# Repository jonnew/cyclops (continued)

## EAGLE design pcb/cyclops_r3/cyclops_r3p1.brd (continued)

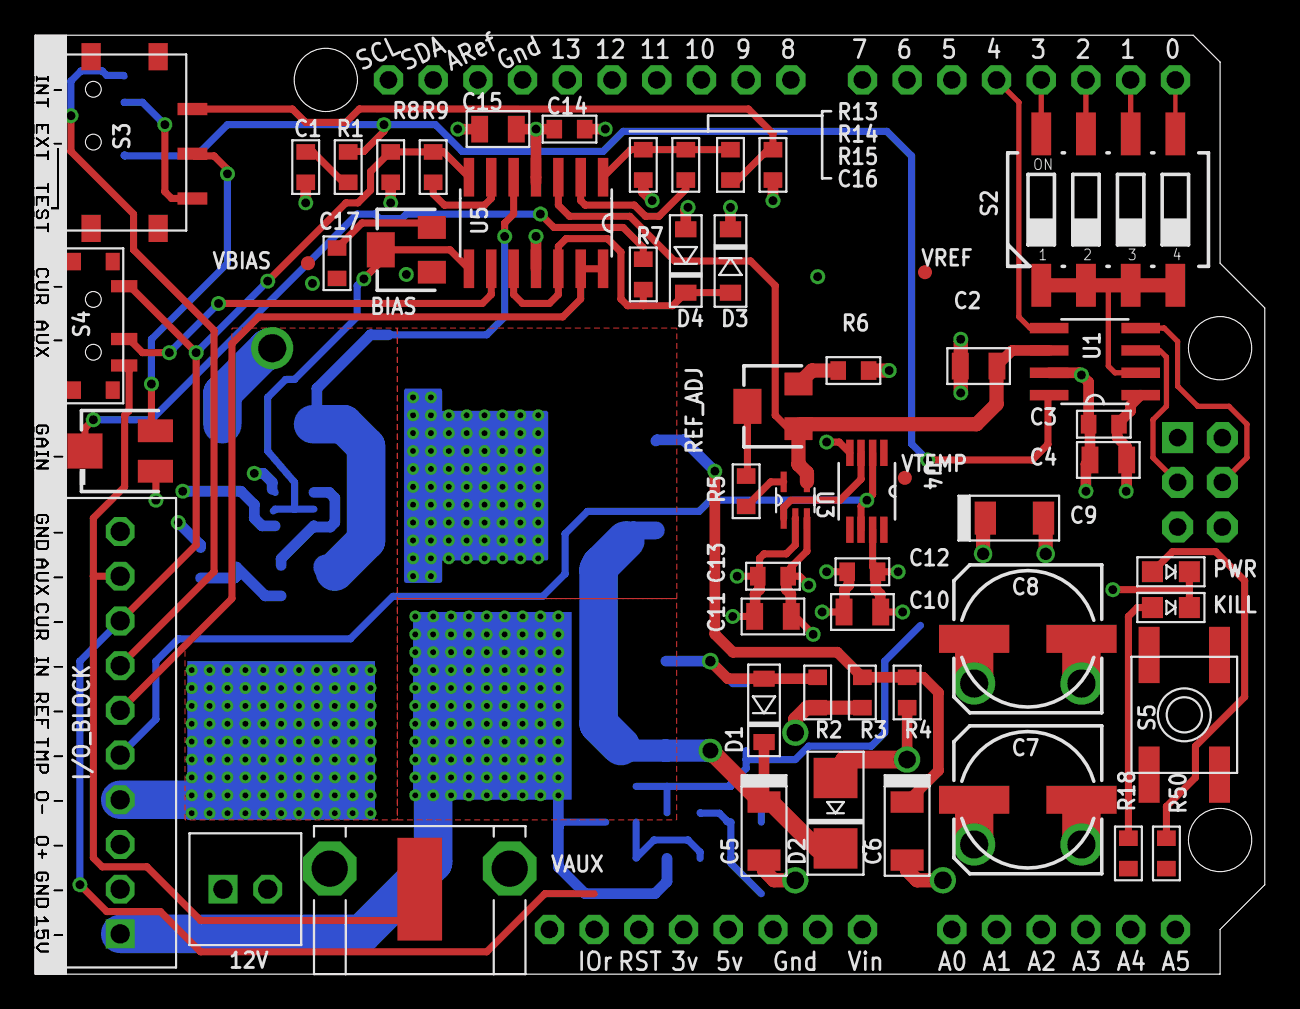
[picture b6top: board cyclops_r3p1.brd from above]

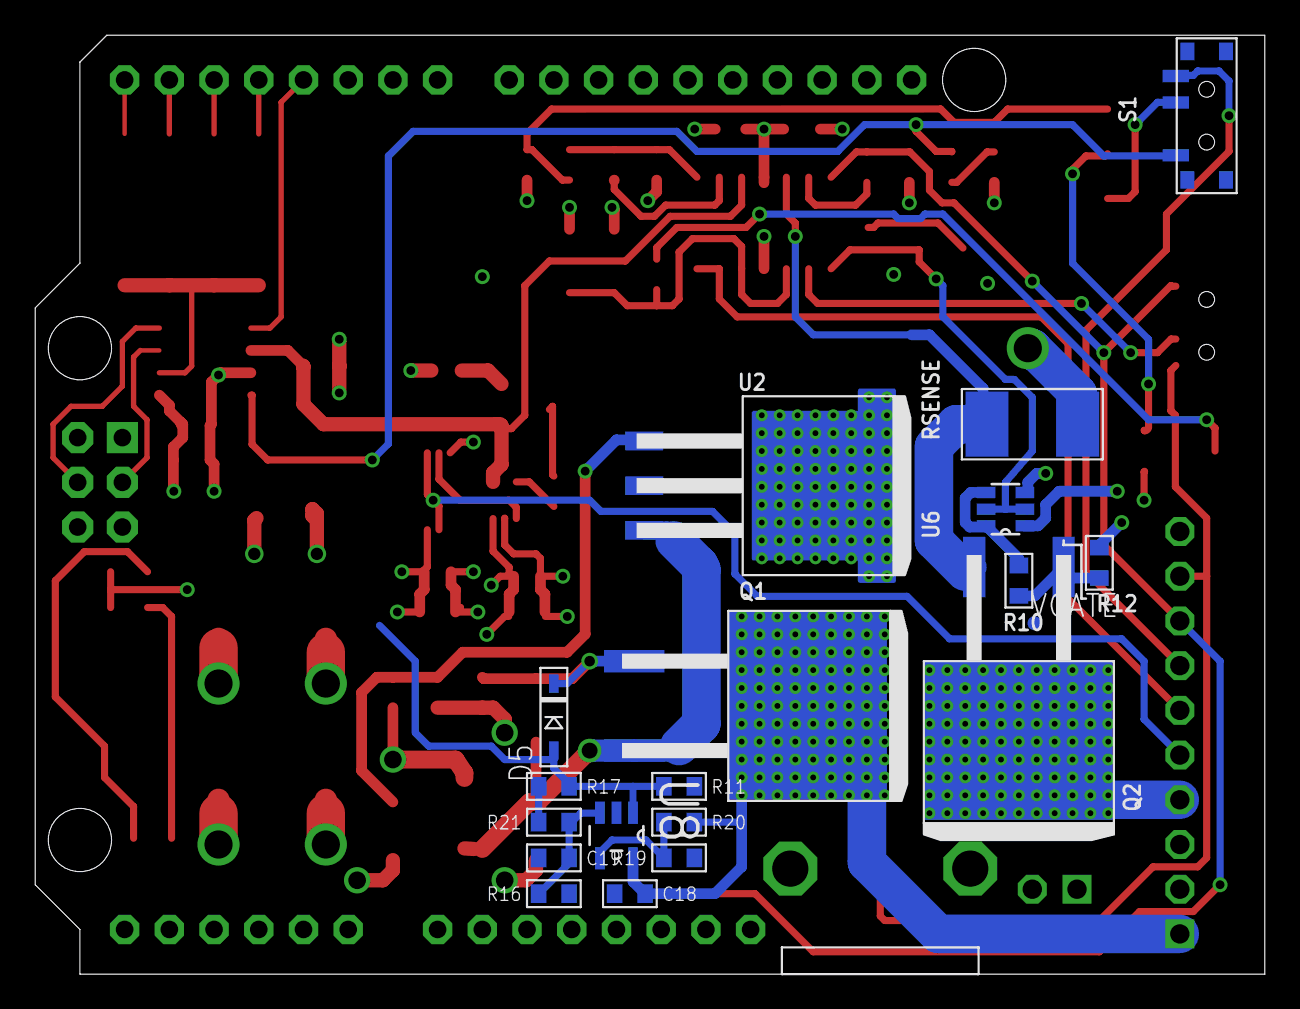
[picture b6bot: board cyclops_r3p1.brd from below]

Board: 4 copper layers, 69.8 x 53.3 mm, 74 parts (19 on the bottom side), 47 nets.

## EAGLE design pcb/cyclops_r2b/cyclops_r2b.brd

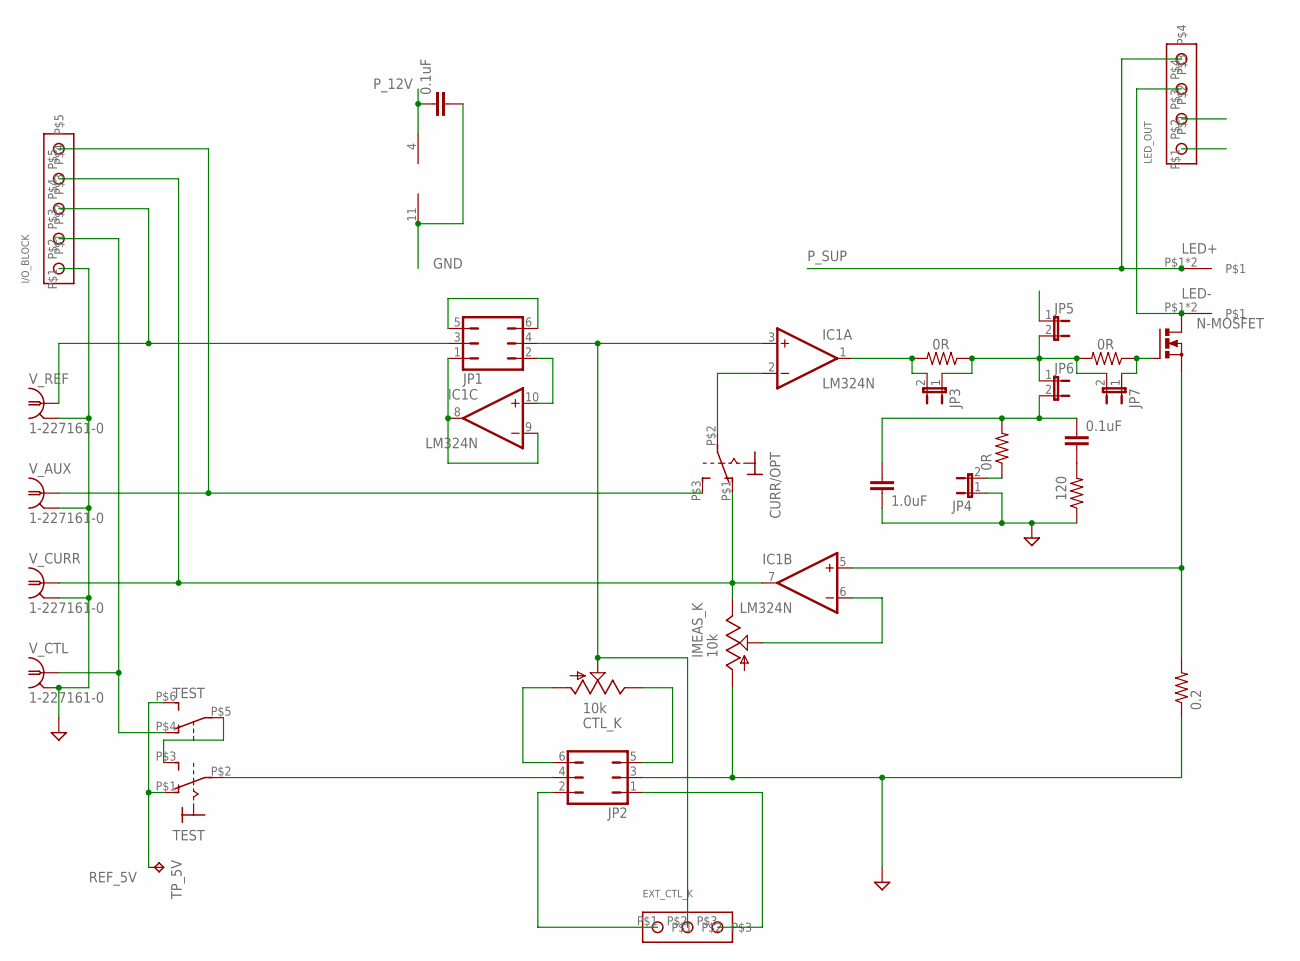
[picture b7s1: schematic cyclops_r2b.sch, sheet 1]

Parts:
C1, C3: 0.1uF; C050-024X044
C2: 1.0uF; C025-024X044
CTL_K: 10k; RJ6S
CURR/OPT: SPST_SWITCH; A_TOGGLE_SPST
EXT_CTL_K: SCREW3
I/O_BLOCK: SCREW5
IC1: LM324N; DIL14
IMEAS_K: 10k; RJ6S
JP1, JP2: JP3Q
JP3, JP4, JP5, JP6, JP7: JP1E; JP1
LED+: BANANA_TO_BOARD
LED-: BANANA_TO_BOARD
LED_OUT: SCREW4
N-MOSFET: PMOSFET_NTO220BH; TO220BH
R1, R2, R4: 0R; 0207/7
R3: 120; 0207/7
R_CURR: 0.2; IMEAS_R
TEST: SP3T_SWITCH; 320-938
TP_5V: TPPAD1-13; P1-13
V_AUX: 1-227161-0; AMP_227161
V_CTL: 1-227161-0; AMP_227161
V_CURR: 1-227161-0; AMP_227161
V_REF: 1-227161-0; AMP_227161

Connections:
GND: C1.2, C2.2, I/O_BLOCK.P$1, IC1.11 (V-), IMEAS_K.A, JP2.3, JP4.1, LED_OUT.P$1, R3.1, R_CURR.1, V_AUX.2 (GND), V_CTL.2 (GND), V_CURR.2 (GND), V_REF.2 (GND); also elsewhere on the board
unnamed: CURR/OPT.P$2, IC1.2 (-IN)
unnamed: IC1.5 (+IN), N-MOSFET.S, R_CURR.2
unnamed: IC1.1 (OUT), JP3.2, R1.2
unnamed: CURR/OPT.P$1 (O), I/O_BLOCK.P$4, IC1.7 (OUT), IMEAS_K.E, V_CURR.1
unnamed: CURR/OPT.P$3 (S), I/O_BLOCK.P$5, V_AUX.1
unnamed: JP2.4, TEST.P$2
unnamed: CTL_K.E, JP2.5
unnamed: CTL_K.S, EXT_CTL_K.P$2, IC1.3 (+IN), JP1.4
unnamed: IC1.8 (OUT), IC1.9 (-IN), JP1.1
unnamed: I/O_BLOCK.P$2, TEST.P$4 (O), V_CTL.1
unnamed: C2.1, C3.1, JP6.2, R2.2
unnamed: CTL_K.A, JP2.6
unnamed: C3.2, R3.2
unnamed: IC1.10 (+IN), JP1.2
unnamed: IC1.6 (-IN), IMEAS_K.S
unnamed: JP1.5, JP1.6
unnamed: I/O_BLOCK.P$3, JP1.3, V_REF.1
unnamed: LED-.P$1, LED-.P$2, LED_OUT.P$3, N-MOSFET.D
unnamed: TEST.P$3 (S), TEST.P$5
unnamed: EXT_CTL_K.P$1, JP2.2
unnamed: EXT_CTL_K.P$3, JP2.1
unnamed: JP4.2, R2.1
unnamed: JP3.1, JP5.2, JP6.1, JP7.2, R1.1, R4.2
unnamed: JP7.1, N-MOSFET.G, R4.1
P_12V: C1.1, IC1.4 (V+), LED_OUT.P$2; also elsewhere on the board
P_SUP: LED+.P$1, LED+.P$2, LED_OUT.P$4; also elsewhere on the board
REF_5V: TEST.P$1 (O), TEST.P$6 (S), TP_5V.TP; also elsewhere on the board

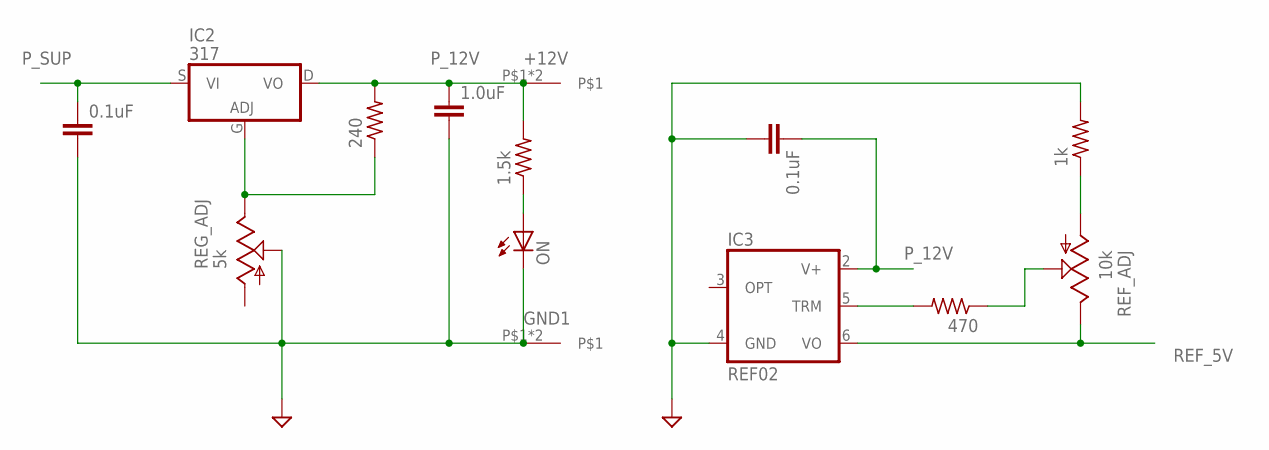
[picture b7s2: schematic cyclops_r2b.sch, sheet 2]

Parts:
+12V: BANANA_TO_BOARD
C4, C6: 0.1uF; C050-024X044
C5: 1.0uF; C025-024X044
GND1: BANANA_TO_BOARD
IC2: 317; TO220BH
IC3: REF02; DIL08-OVAL
ON: LED3MM
R5: 240; 0207/7
R6: 1.5k; 0207/7
R7: 470; 0207/7
R8: 1k; 0207/7
REF_ADJ: 10k; RJ6S
REG_ADJ: 5k; RJ6S

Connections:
GND: C4.2, C5.2, C6.2, GND1.P$1, GND1.P$2, IC3.4 (GND), ON.K (C), R8.2, REG_ADJ.S; also elsewhere on the board
unnamed: IC2.G (ADJ), R5.1, REG_ADJ.E
unnamed: IC3.5 (TRM), R7.2
unnamed: R7.1, REF_ADJ.S
unnamed: R8.1, REF_ADJ.A
unnamed: ON.A, R6.1
P_12V: +12V.P$1, +12V.P$2, C5.1, C6.1, IC2.D (VO), IC3.2 (V+), R5.2, R6.2; also elsewhere on the board
P_SUP: C4.1, IC2.S (VI); also elsewhere on the board
REF_5V: IC3.6 (VO), REF_ADJ.E; also elsewhere on the board

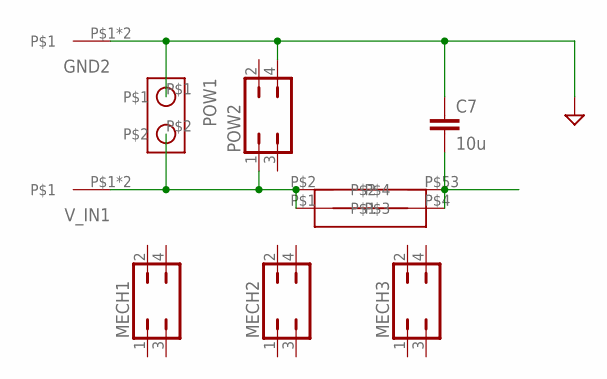
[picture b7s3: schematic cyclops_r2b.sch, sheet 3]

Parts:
C7: 10u; C025-024X044
GND2: BANANA_TO_BOARD
MECH1, MECH2, MECH3: JP2Q
POW1: SCREW2
POW2: JP2Q
U$1: FUSE >2A; NXT-FUSE
V_IN1: BANANA_TO_BOARD

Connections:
GND: C7.1, GND2.P$1, GND2.P$2, POW1.P$1, POW2.4; also elsewhere on the board
P_SUP: C7.2, U$1.P$4, U$1.P$53; also elsewhere on the board
P_SUP_BEFORE: POW1.P$2, POW2.1, U$1.P$1, U$1.P$2, V_IN1.P$1, V_IN1.P$2

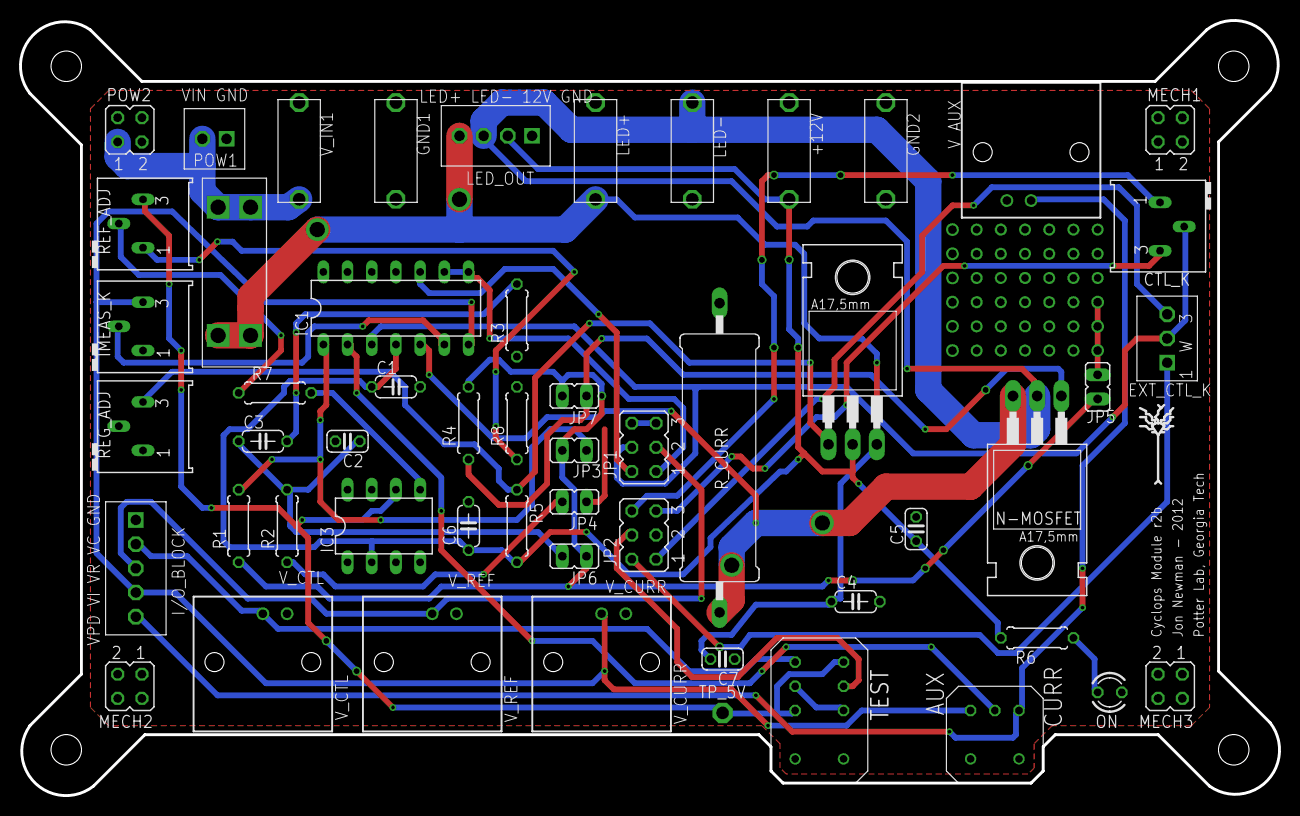
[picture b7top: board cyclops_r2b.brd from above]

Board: 2 copper layers, 132.2 x 81.4 mm, 54 parts (0 on the bottom side), 34 nets.

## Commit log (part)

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2014-08-21 Added digital overcurrent protection.
2014-08-22 Minor cleanup.
2014-08-24 Removed temp vim files.
2014-09-04 Cleaned up BOM.
2014-09-04 Slight BOM update.
2014-09-15 Final very minor changes to r3.3. before fabrication.
2014-10-04 More work on driver.
2014-10-06 The base library is functional. Includes over-current protection and waveform generation features.
2014-10-06 Work on trigger interupt handling.
2014-10-07 Added an over-current protection example.
2014-10-10 Front panel dimensions have been tested and look good. Started integrating light pipes on front panel LEDs. The LEDs need to be moved and swapped for normal verical ones.
2014-10-14 Finished front and rear panel layout. Started PCB version.
2014-10-15 Organization.
2014-10-21 Minor updates.
2014-10-26 Some layout changes to make ergonomic. Updated BOM.
2014-10-30 Almost done with panels.
2014-10-30 BOM update.
2014-11-09 Added automatic logic level conversion on trigger line.
2014-11-16 Updated TODO.
2014-11-20 Added a note.
2014-11-22 More spice simulations.
2014-11-23 Spice update.
2014-11-24 Added spice simulation of negative rail generation.
2014-11-25 New schematic should be finished. Double check and then layout board.
2014-11-26 Started laying out switching inverter.
2014-11-30 More layout.
2014-12-19 Updates to TODO. Fixed MAX4564 package type.
2014-12-21 Layout of rev. 3.5. It needs to be double checked before fabrication.
2014-12-21 Minor layout changes.
2014-12-22 Updated panels for revision 3.5. Updated BOM for revision 3.5. Did inventory check to see what nees to be ordered.
2014-12-23 Almost ready to fabricate PCB. I need to do one last look over, concentrating on schematic.
2014-12-26 Built the LT1963 circuit next to the LM317, I will now replace the LM317.
2014-12-26 Added LM1936 to the board.
2014-12-28 Updated BOM and small layout changes. Ready to print.
2014-12-30 Ready to fabricate. This is revision 3.5.
2015-01-03 Minor BOM update.
2015-01-19 More TODOs and small fixes to circuit.
2015-01-22 Implemented some more TODOs.
2015-01-31 Small changes to spice. Need to bench test.
2015-02-08 Made schematic changes after testing latest spice simulations at the bench.
2015-02-15 Updated gerbers to rev 3.5A.
2015-02-16 Changed the test point labels, again.
2015-02-17 Started implementing documentation.
2015-02-25 Fixed the front panel design. This is revision 3.5A.
2015-02-25 Documentation updates.
2015-02-28 Updated PDF version of schematic.
2015-03-29 Refixed the incorrect labels on the jumper pads.
2015-04-02 More TODOs
2015-04-12 Started updating the docs
    - These will eventually be moved into the README.md
    - Need to integrate figures and create a mirrored PDF using pandoc.
2015-05-31 Minor README.md update.
2015-06-08 Got rid of negative supply source jumper.
2015-06-13 Rename file.
2015-07-02 DOC.md update.
2015-07-21 Sung-Yon is uploading some Cyclops pictures while trying to learn GitHub
2015-07-28 Fixed image display issue in DOC.md.
2015-07-28 jon's and my edit caused conflicts
2015-07-28 trying capitalized .JPG for Figs 3 and 4
2015-07-29 Updates to DOC.md. Need to think about how to make markdown pandoc friendly.
2015-07-30 More organization.
2015-07-30 Resize images to 400px max.
2015-07-30 Updates to DOC.md to make more pandoc friendly
    - I want to revert all the figure resizing changes because they look
    really bad now.
2015-08-02 Fixed file names.
2015-08-03 Updates to MANUAL.*.
2015-08-03 Many undates to MANUAL.md
    - About time to merge back into master branch.
    - All images reverted to original size
    - Manual is still under construction, but is complete enough to start
    being useful for people.
2015-08-04 Added some performance measures to the manual.
2015-08-05 Some minor updates to MANUAL.*
2015-08-19 Some recorganization and updates to manual.
2015-08-30 Minor silkscreen changes.
2015-10-30 A few changes made to comply with CircuitHub stuff
    - Almost ready to do a circuit hub run.
2015-12-02 Minor fix to the input circuit.
2015-12-15 Replaced edge mount BNC with cheaper alternative
    - Less than half the price
    - Much more available (made by molex)
    - Huge BOM money saver
    - Worried about production run with this many changes...
2015-12-17 Repo reorganization.
2015-12-31 Some very minor changes during final 3.5c assembly.
2016-01-04 Final changes to board after rev 3.5c construction and testing.
2016-01-27 File format update
    File is incorporated into the repo, rather than a text file with a url
    pointing at it. Removed date and spaces in title.
2016-01-28 Update MANUAL.md
    Markdown style retrieve link to Bilateral fiber coupled LED.
2016-02-03 Updates to QC procedure.
2016-02-03 README update.
2016-02-21 Lots of cleanup for 3.5D tag.
    - Got rid of versioning info in file names
    - Got rid of old BOM managment method since we can just point to
    circuithub instead
2016-02-21 More cleanup.
2016-02-21 Fixed broken links in manual.
2016-02-28 Nearly done with getting started guide.
    - There are couple of TODOs in the document that need to be taken care
    of
    - Document also points to full manual for documentaiton on some stuff
    (e.g. M8 connector install) that is not currently there.
2016-03-03 Documentation improvements.
2016-03-24 Small edit to kit manual.
2016-03-25 Forgot to add file.
2016-04-04 Update MANUAL.*
    - Fixes #3
    - Partially merged the kit assembly instructions with the main manual
    - Added a bunch of TODOs that generally concern interfacing the cyclops
    with external devices and LEDs, installing the Arudino, programming
    the Arrduino etc.
2016-04-04 More MANUAL.* updates
2016-04-19 Update README.md
    Added TODO for Rev. 3.6
2016-04-19 Tested Task objects (passed)
    Compiles and executes as expected.
    All Header field extraction using macros in RPC_defs.h, any change in RPC would reflect here, no need to change code elsewhere!
2016-04-19 Defined Waveform methodswq
2016-04-20 Added reset in Source, and Waveform example
    reset() is also virtual (since resetting sources cannot always be setting cur_ind = 0)
    Waveform example ping pongs between 2 (sin(t))^2 gen_Source objs
2016-05-03 Updated thorlabs LED connection instructions.
2016-05-07 Refactored the Waveform and Source classes
    Variables and class-names are better now.
    storedSource members are const*, so they won't edit the data arrays.
    Updated documentation.
    Apart from that made stylistic changes.
    Added keywords.txt
    Tested examples, made them more readable, less cluttered
2016-05-29 Modified Waveform to support scheduling. Added non-blocking SPI
    * nbSPI defines a few helper functions and an ISR for interrupt driven SPI
    * `Waveform::prepare`
    - begins an SPI transfer if in `PREPARING` state
    - can handle multi-byte transfers for a transaction.
    * `Cyclops::selectChip` and `Cyclops::deselectChip()` needed as all lookup tables are private.
    * Added the test for Queue.
2016-05-31 Added the Timer ISR, scheduler logic.
    * Using TimerOne library by Paul Stoffregen.
    * Waveform::process() is called by CPU scheduler
    * the `cyclops_timer_ISR` is pretty lightweight.
    * The pre-instantiated `waveformList` is the heart of this library.
2016-06-03 Source code reorganization.
2016-06-07 Added documentation and examples
    * nbSPI is not effective for Arduino devices, see docs/nbSPI
    * nbSPI tested [pass] and documented.
    * Added logo to docs :)
    * Fixed subtle bug in Waveform::outFrame_id, it should be initialised to DAC_BLOCK_SIZE.
2016-06-08 Fixed WaveformList (atleast for single channel)
    Now I can confidently start testing and porting on teensy
2016-06-11 Added head to head comparison table to MANUAL.md.
2016-06-15 Fixed Timer issues, made library.
    Also,
    * Waveform_t is complete. Can handle upto 4 channels
    * TimerOne fixed for our use.
    * Added example wave2_teensy. Uses latest libs
2016-06-17 More teensy layout.
2016-06-18 RPC draft implementation, see /src/teensy/rpc_loop
    * Serial comms are non-blocking
    * Fixed typos in RPC_defs.h (still buggy)
    * Added logic to task, Queue
    * Changed holdTime return type (once again) to uint32_t
    * Changed constructor calls to accomodate for N_SHOT, see wave2_teensy.ino
2016-06-21 RPC v1 implementation Complete \o/
    * added squareSource commands and changed LDAC temporarily
    * Fixed typo in ISR, also changed window size.
    * added RPC implementation in Task.cpp
    * added TScale, VScale, DC offset, squareSource, constHoldTime (for gen. Source)
    * 2 constructors for gen. Source
    * Tested rpc_loop.ino and all_waves.ino, other examples might be broken
2016-06-22 More docs and a CyclopsLib namespace
    * All stray functions or global vars are now in this namespace.
    * Added documentation on Task, readSerialAndPush, etc
    *
2016-07-05 Ticking off preparations for 3.6 layout.
2016-07-08 Lots of minor circuit mods
    - Replace OC SPDT with a SPST with better bandwidth and larger voltage
    rail capabilities since id does not need the other terminal
    - Spice modeling of input circuitry
    - Etc
2016-07-10 Started addining buck converter for digital rail.
2016-07-12 Almost done with layout.
2016-07-14 More routing. Need to do ERC/DRC at this point.
2016-07-15 Silkscreen work.
2016-07-16 Very close to finished with Rev. 3.6-beta PCB
    - A couple lingering TODOs as stated on the first page of the schematic.
    Mostly mechnical/overlap issues at this point
2016-07-30 Added Board identification and more RPC for GUI
    * Board identification LUT added.
    * gitignore -> ignore .pyc
    * Added REGISTER_SOURCE_LIST macro.
    * The GUI example has a separate "MySources.h"
    * Added Waveform::groundAll(), to turn off LEDs when experiment is stopped.
    * Added Source::resetAll() to reset all (registered) Sources when experiment is stopped, in preparation of re-launch.
2016-07-30 Removed defunct jonnew-lbr submodule.
2016-08-01 Fixed a few minor issues found during circuit hub uploading process.
2016-08-05 Update MANUAL.md
    Fixed link for Arduino Compatible Reflow Oven Controller Shield. Added link for DIY reflow oven.
2016-08-25 Minor circuit changes made during testing.
2016-08-29 Added LTM8020 datasheet.
2016-10-14 Moved the LED to drain side of FET
    - This prevents Vgs from dropping in nonlinear fashion as LED turns on.
    Not sure why LED was on low side to begin with.
2016-10-22 Final circuit changes before production.
2016-10-31 Started aluminum front panel design
    - Using front panel express for now. Perhaps a PCB panel would be best
    though.
2016-11-05 Started PCB version of the panels because it will be the most cost effective.
2016-11-27 Minor fixes after assembly of 3.6
2016-12-19 Final fixes for 3.6
    - Fixed issue with parasitic oscillation in BJT booster stage
    - Fixed issue with bandwidth limit selection by simply removing cold
    switch and using the straight panel switch -- extra trace length does
    not matter because it engages the BW limit (self correcting)
    - Should be ready for production and master merge
2017-01-04 Thermal fixes after testing.
2017-02-12 Level shifter and improvied thermal dissipation
    - Level shifter is required since DAC's logical thresh is 0.7 VDD which
    is 6V
    - Improvied thermal dissiplation for FET
    - Replaced finicky analog switch with a signal relay.
2017-03-10 Ready for 3.6 production
    - These designs are up to date for 3.6 production
    - I need to create an assembly manual before moving forward
2017-04-17 More pre-production fixes for Filipe.
    - Better cutouts on Exapansion B in panel
    - Panel alignment
    - Schematic fixes (remove teensy cut trace/diode requirement)
2017-04-19 Removed GSOC code for now.
    - I hope that it can be merged in from the gsoc-dev branch in the
    future.
2017-06-26 Removed non-commercial part of CC license
    - Cyclops will begin commercial production, so that had to go.
    - Some README and MANUAL updates
2017-07-15 Compensation capacitor to silince ringing in BJT booster stage
    - Seems to cure all ringing for different LEDs and cable lengths
2017-10-03 Moved to manual build script Makefile
2017-10-21 Update PRODUCT.TXT
    - Fixed some grammatical issues and extended text to beyond OEPs
2017-10-26 Update MANUAL.md
    - Removed confusing self-references
2018-01-30 dac_generate_waveform delay fix
    - Prevent extra delay in dac_generate_waveform due to delaying after loading last point in waveform sequence
2018-06-23 MANUAL update
    - Switch to pandoc markdown
    - Added descriptions of device controls
    - Lots of other fixes
2018-06-25 Updates to MANUAL
    - Also minor PCB silk screen fixes
2019-01-03 Update README.md
    - More info about what Cyclops actually is.
2020-07-14 Update Cyclops.h
    - Fixes #21
    - RISING/FALLING interrupt edge specification was misidentified as CHANGED instead of the actual macro, which is CHANGE
2020-09-17 Changes to revision 3.7 after in the field testing
    - Some small moves on the panel and pcb for manufacturing purposes
2021-04-10 Decreased screws external rings to hide exposed pads below screw heads.
2021-04-10 Split panel into two files (front and back panel)
